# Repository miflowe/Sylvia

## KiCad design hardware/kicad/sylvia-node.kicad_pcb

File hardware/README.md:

# Sylvia Node hardware

Home wildfire-smoke and smoulder sensor for the Sylvia app. **Tier B "Resilient home"** is the board being
built: ESP32-S3 + RAK3172 LoRaWAN backup, Sensirion SEN66, SPEC CO cell + LMP91000, BME688, solar charging
into 2× LiFePO4 18650, 4-layer PCB for JLCPCB. Status and next steps: **`PROGRESS-hardware.md`**.

## Start here
| You are… | Read |
|---|---|
| Reviewing the design | `docs/requirements.md` → `docs/block-diagram.md` → `docs/reference-circuits.md` → `docs/review-checklist.md` |
| Doing the PCB layout | `docs/layout-guide.md`, then open `kicad/sylvia-node.kicad_pro` in KiCad 9 |
| Writing firmware | `firmware/README.md`, `docs/pin-map.md`, `docs/i2c-map.md` |
| Making the deck slide | `docs/tiers.md` |
| Ordering parts | `parts/parts.csv` (all tiers, LCSC numbers, price snapshot), `kicad/bom-draft.csv` (Tier B board) |

## Folder map
| Path | What |
|---|---|
| `kicad/sylvia_node.py` | **Schematic as code** (SKiDL). The source of truth for the circuit |
| `kicad/sylvia-node.net` | Generated KiCad netlist · `sylvia_node.erc` ERC report · `bom-draft.csv` |
| `kicad/sylvia-node.kicad_pcb` | Starter board (all footprints + nets, unplaced) for the layout |
| `kicad/lib/` | Project library: `sylvia.kicad_sym`, `sylvia.pretty/`, `3dmodels/` |
| `parts/` | `parts.csv`, `datasheets.csv` (URL + sha256), download batch lists |
| `datasheets/` | Local PDFs only (copyrighted, gitignored): `tools/fetch_datasheets.py` re-fetches them |
| `docs/` | Requirements, block diagram, reference circuits, power budget, pin + I2C maps, layout guide, checklists, tiers |
| `firmware/` | ESP-IDF firmware; pure-C logic tested on the host |
| `tools/` | Generators and checks (below) |

## Setup (Windows, once)
```bash
python -m venv hardware/.venv
```
```bash
hardware/.venv/Scripts/python -m pip install easyeda2kicad skidl ziglang pytest
```
KiCad 9.0.x must be installed at `C:/Program Files/KiCad/9.0` (used for its libraries, `kicad-cli` and Python).

## Commands
| Command | Does |
|---|---|
| `hardware/.venv/Scripts/python -I hardware/tools/verify_all.py` | **Every check**: ERC, pin/pad, footprints, pin map, power budget, firmware tests, LCSC numbers |
| `hardware/.venv/Scripts/python -I hardware/kicad/sylvia_node.py` | Regenerate netlist + ERC + draft BOM |
| `python -I hardware/tools/build_parts.py` | Refresh `parts.csv` prices/stock from JLCPCB (snapshot) |
| `python -I hardware/tools/build_library.py` | Rebuild the KiCad library from KiCad + EasyEDA + our own parts |
| `"C:/Program Files/KiCad/9.0/bin/python.exe" hardware/tools/make_starter_pcb.py` | Starter board (refuses to overwrite) |
| `python -I hardware/tools/jlc_export.py` | Gerbers + JLCPCB BOM/CPL from the finished board |
| `python -I hardware/tools/power_budget.py` | Regenerate `docs/power-budget.md` |

## Licences
KiCad library content: CC-BY-SA-4.0 with the KiCad library exception. EasyEDA/LCSC-derived symbols, footprints
and `.wrl` models: LCSC/EasyEDA library terms. Manufacturer STEP models and datasheets stay local (gitignored).
Our own footprints and code: the repository's licence.

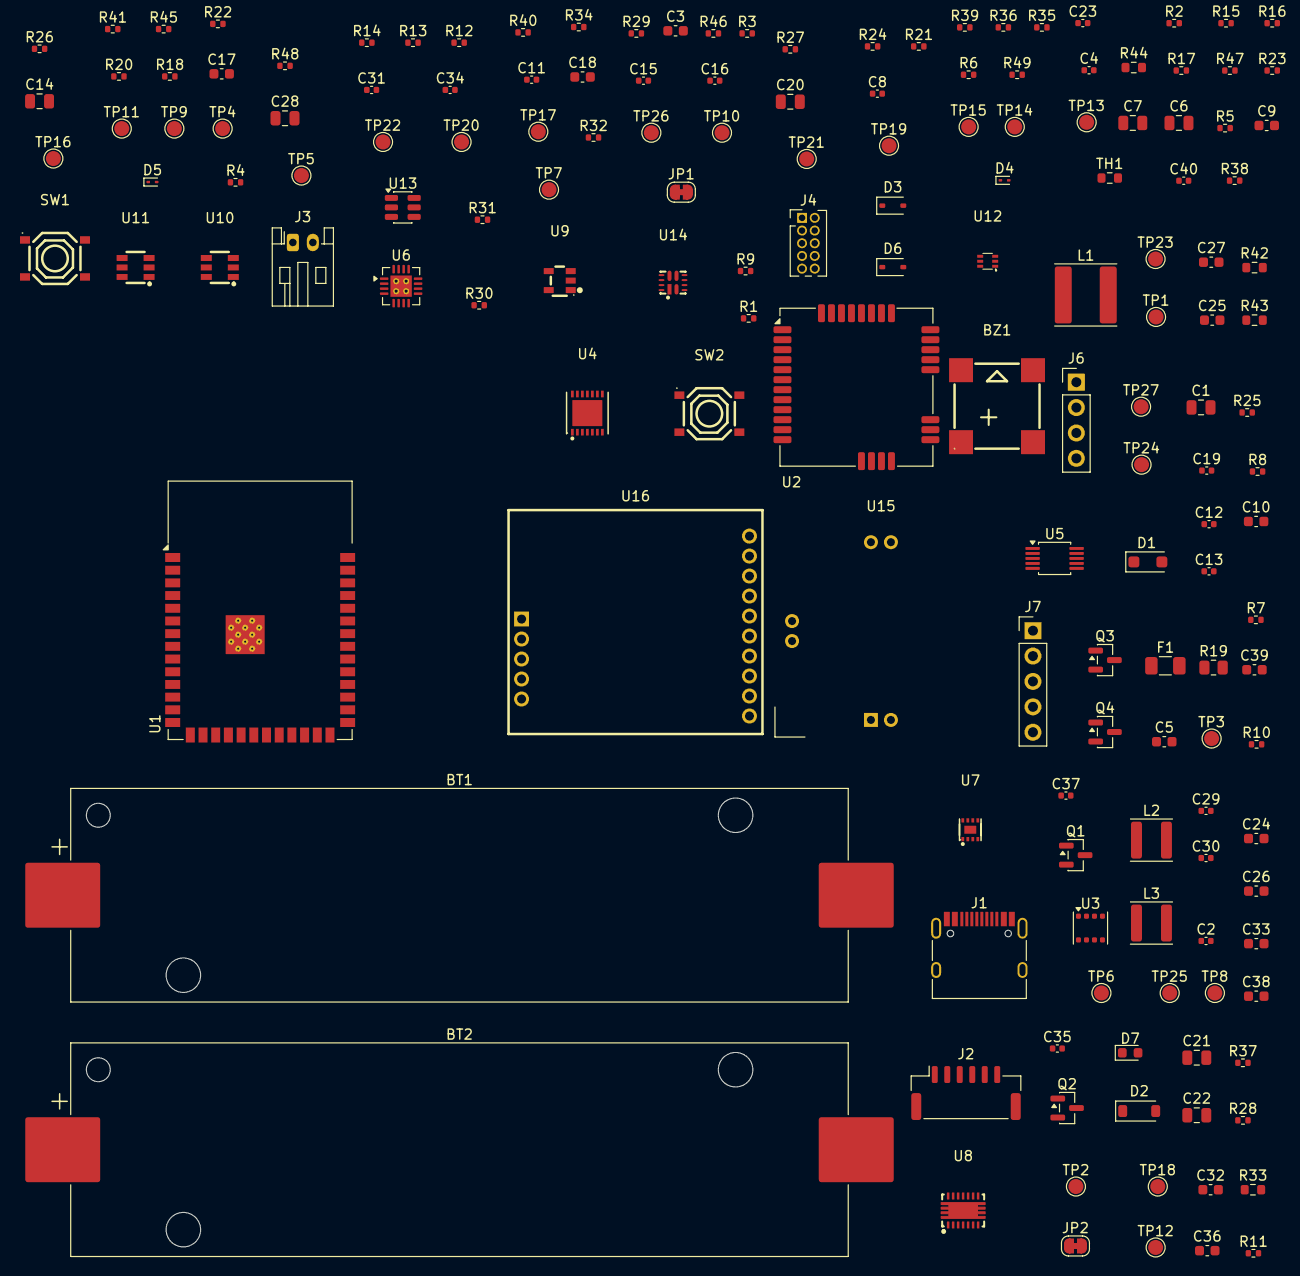
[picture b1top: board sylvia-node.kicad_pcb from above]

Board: 2 copper layers, 161 parts (0 on the bottom side), 88 nets, no tracks yet.

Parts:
BT1, BT2: LiFePO4 18650; BatteryHolder_Keystone_1042_1x18650
BZ1: MLT-8530; BUZ-SMD_4P-L8.5-W8.5-P8.50-BR
C1, C6, C7, C14, C20, C21, C22, C28: 22uF; C_0805_2012Metric
C2, C8, C11, C12, C13, C15, C16, C19, C29, C30, C31, C34, C35, C37, C40: 100nF; C_0402_1005Metric
C3, C9, C10, C24, C26, C33, C38, C39: 1uF; C_0603_1608Metric
C4: 4.7nF; C_0402_1005Metric
C5: 4.7uF; C_0603_1608Metric
C17, C18, C25, C27, C32, C36: 10uF; C_0603_1608Metric
C23: 1nF; C_0402_1005Metric
D1: SMF12A; D_SOD-123F
D2: B5819W; D_SOD-123
D3: 1N5819WS; D_SOD-323
D4, D5: ESD9B5.0ST5G; D_SOD-923
D6: 1N4148WS; D_SOD-323
D7: green; LED_0603_1608Metric
F1: 2A; Fuse_1206_3216Metric
J1: TYPE-C-31-M-12; USB_C_Receptacle_HRO_TYPE-C-31-M-12
J2: SEN66; JST_GH_SM06B-GHS-TB_1x06-1MP_P1.25mm_Horizontal
J3: SOLAR 6V; JST_PH_S2B-PH-K_1x02_P2.00mm_Horizontal
J4: PMSA003I; PinHeader_2x05_P1.27mm_Vertical
J6: UART0; PinHeader_1x04_P2.54mm_Vertical
J7: RAK SWD; PinHeader_1x05_P2.54mm_Vertical
JP1: JP1 VBAT->SYS; SolderJumper-2_P1.3mm_Bridged_RoundedPad1.0x1.5mm
JP2: JP2 3V3 out; SolderJumper-2_P1.3mm_Bridged_RoundedPad1.0x1.5mm
L1: 15uH; L_Sunlord_SWPA6045S
L2: 1.5uH; L_Sunlord_SWPA4020S
L3: 1uH; L_Sunlord_SWPA4020S
Q1, Q2: AO3400A; SOT-23
Q3, Q4: 2N7002; SOT-23
R1, R2, R15, R16, R22, R36, R45, R46: 10k; R_0402_1005Metric
R3, R34, R35, R39, R40: 1k; R_0402_1005Metric
R4: 100R; R_0402_1005Metric
R5, R6, R10, R11, R13, R14, R21, R25, R26, R28, R37, R38, R48: 100k; R_0402_1005Metric
R7, R8: 5.1k; R_0402_1005Metric
R9, R23: 1M; R_0402_1005Metric
R12: 270k; R_0402_1005Metric
R17: 4.42k; R_0402_1005Metric
R18: 21.5k; R_0402_1005Metric
R19: 0.1R; R_0805_2012Metric
R20: 71.5k; R_0402_1005Metric
R24: 180k; R_0402_1005Metric
R27: 732k; R_0402_1005Metric
R29, R30, R31, R32: 4.7k; R_0402_1005Metric
R33, R42, R43, R44: 0R; R_0603_1608Metric
R41: 0R; R_0402_1005Metric
R47: 309k; R_0402_1005Metric
R49: 80.6k; R_0402_1005Metric
SW1: RESET; SW-SMD_4P-L5.1-W5.1-P3.70-LS6.5-TL_H1.5
SW2: BOOT; SW-SMD_4P-L5.1-W5.1-P3.70-LS6.5-TL_H1.5
TH1: 10k B3380; R_0603_1608Metric
TP1: TAMPER; TestPoint_Pad_D1.5mm
TP2: TAMPER_GND; TestPoint_Pad_D1.5mm
TP3: IO48; TestPoint_Pad_D1.5mm
TP4: VBUS; TestPoint_Pad_D1.5mm
TP5: SOLAR_IN; TestPoint_Pad_D1.5mm
TP6: CHG_STAT1; TestPoint_Pad_D1.5mm
TP7: CHG_STAT2; TestPoint_Pad_D1.5mm
TP8: VBAT; TestPoint_Pad_D1.5mm
TP9: VCHG; TestPoint_Pad_D1.5mm
TP10: FG_ALRT; TestPoint_Pad_D1.5mm
TP11: BB_EN; TestPoint_Pad_D1.5mm
TP12: BB_PG; TestPoint_Pad_D1.5mm
TP13: 3V3; TestPoint_Pad_D1.5mm
TP14, TP15: GND; TestPoint_Pad_D1.5mm
TP16: 3V3_SEN; TestPoint_Pad_D1.5mm
TP17: 3V3_ALT; TestPoint_Pad_D1.5mm
TP18: 5V_ALT; TestPoint_Pad_D1.5mm
TP19: I2C1_SDA; TestPoint_Pad_D1.5mm
TP20: I2C1_SCL; TestPoint_Pad_D1.5mm
TP21: I2C0_SDA; TestPoint_Pad_D1.5mm
TP22: I2C0_SCL; TestPoint_Pad_D1.5mm
TP23: 3V3_CO; TestPoint_Pad_D1.5mm
TP24: CO_VOUT; TestPoint_Pad_D1.5mm
TP25: AIN3; TestPoint_Pad_D1.5mm
TP26: LORA_TX; TestPoint_Pad_D1.5mm
TP27: LORA_RX; TestPoint_Pad_D1.5mm
U1: ESP32-S3-WROOM-1-N8R8; ESP32-S3-WROOM-1
U2: RAK3172-9-SM-I; RAK3172
U3: BME688; Bosch_LGA-8_3x3mm_P0.8mm_ClockwisePinNumbering
U4: LMP91000SDX/NOPB; WSON-14_L4.0-W4.0-P0.50-BL-EP-1
U5: ADS1115IDGSR; VSSOP-10_3x3mm_P0.5mm
U6: BQ24650RVAR; Texas_RVA_VQFN-16-1EP_3.5x3.5mm_P0.5mm_EP2.14x2.14mm_Therma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
U7: MAX17048G+T10; TDFN-8_L2.0-W2.0-P0.50-BL-EP1.2
U8: TPS63020DSJR; VSON-14_L4.0-W3.0-P0.50-BL-EP_TI_DSJ
U9: TPS3840PL27; SOT-23-5_L2.9-W1.6-P0.95-LS2.8-BR
U10, U11: TPS22918; SOT-23-6_L2.9-W1.6-P0.95-LS2.8-BR
U12: TPS61023; SOT-563_L1.6-W1.2-P0.50-LS1.6-BR
U13: USBLC6-2SC6; SOT-23-6
U14: TPS2121RUXR; VQFN-HR-12_L2.5-W2.0-P0.50-BL
U15: 110-102; SPEC_110-102_THT
U16: ZE07-CO; SENSOR-TH_ZE07-CO

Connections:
3V3: BZ1.1, C1.1, C2.1, C24.1, C29.1, C30.1, D6.1, J6.1, JP2.2, R1.1, R2.1, R6.1, R15.1, R16.1, R22.1, R31.1, R32.1, R33.1, R36.1, R42.1, TP13.1, U1.2, U3.2, U3.6, U3.8, U10.1, U11.1
3V3_ALT: C26.1, C27.1, L3.1, TP17.1, U11.5, U11.6, U12.2, U12.3
3V3_CO: C31.1, C32.1, C35.1, R33.2, R34.1, TP23.1, U4.6, U5.1, U5.8
3V3_LORA: C36.1, C37.1, J7.1, R42.2, R45.1, U2.24
3V3_REG: C20.1, C21.1, C22.1, JP2.1, R23.1, U8.4, U8.5
3V3_SEN: C25.1, J2.1, J2.6, R29.1, R30.1, TP16.1, U10.5, U10.6
5V_ALT: C28.1, J4.1, J4.2, R27.1, TP18.1, U12.6, U16.15
ADC_AIN3: R38.1, TP25.1, U5.7
ADC_RDY: R36.2, U1.24, U5.2
ALT_UART_RX: R39.2, U1.34
ALT_UART_TX: R40.1, U1.35
BB_EN: TP11.1, U8.12, U9.1
BB_FB: R23.2, R24.1, U8.3
BB_L1: L2.1, U8.8, U8.9
BB_L2: L2.2, U8.6, U8.7
BB_PG: TP12.1, U8.14
BST_FB: R27.2, R28.1, U12.1
BST_SW: L3.2, U12.5
BUZZER: R4.1, U1.8
BUZ_D: BZ1.4, D6.2, Q3.3
BUZ_G: Q3.1, R4.2, R5.1
CC1: J1.A5, R7.1
CC2: J1.B5, R8.1
CHG_BTST: C11.1, D3.1, U6.16
CHG_HIDRV: Q1.1, U6.15
CHG_INHIBIT: Q4.1, R14.1, U1.18
CHG_LODRV: Q2.1, U6.13
CHG_PH: C11.2, L1.1, Q1.2, Q2.3, U6.14
CHG_SRP: C12.1, L1.2, R19.1, U6.10
CHG_STAT1: R15.2, TP6.1, U1.20, U6.3
CHG_STAT2: R16.2, TP7.1, U1.21, U6.5
CHG_TS: R17.2, R18.1, TH1.1, U6.4
CHG_VFB: R20.2, R21.1, U6.8
CO_ADC_ESP: R35.2, U1.39
CO_CE: U4.14, U15.5
CO_RE: U4.13, U15.4
CO_VOUT: R35.1, TP24.1, U4.8, U5.4
CO_WE: U4.12, U15.1, U15.6
EN_ALT: R26.1, U1.17, U11.3
EN_SEN: R25.1, U1.12, U10.3
ESP_BOOT: R2.2, SW2.1, SW2.2, U1.27
ESP_EN: C3.1, R1.2, SW1.1, SW1.2, U1.3
FG_ALRT: R22.2, TP10.1, U1.19, U7.5
GND: BT1.2, BT2.2, C1.2, C2.2, C3.2, C4.2, C5.2, C6.2, C7.2, C8.2, C9.2, C10.2, C13.2, C14.2, C15.2, C16.2, C17.2, C18.2, C19.2, C20.2, C21.2, C22.2, C23.2, C24.2, C25.2, C26.2, C27.2, C28.2, C29.2, C30.2, C31.2, C32.2, C33.2, C35.2, C36.2, C37.2, C38.2, C39.2, C40.2, D1.2, D4.2, D5.2, D7.1, J1.A1, J1.A12, J1.B1, J1.B12, J2.2, J2.5, J2.MP, J3.2, J4.3, J4.4, J6.4, J7.5, Q2.2, Q3.2, Q4.2, R5.2, R7.2, R8.2, R9.2, R11.2, R13.2, R14.2, R18.2, R21.2, R24.2, R25.2, R26.2, R28.2, R37.2, R38.2, R46.2, R48.2, R49.2, SW1.3, SW1.4, SW2.3, SW2.4, TH1.2, TP2.1, TP14.1, TP15.1, U1.1, U1.40, U1.41, U2.11, U2.17, U2.18, U2.23, U2.28, U3.1, U3.5, U3.7, U4.1, U4.2, U4.7, U4.15, U5.3, U6.11, U6.17, U7.1, U7.4, U7.6, U7.9, U8.2, U8.13, U8.15, U9.3, U10.2, U11.2, U12.4, U13.2, U14.3, U14.4, U14.5, U14.9, U14.12, U16.5, U16.14
I2C0_SCL: R32.2, TP22.1, U1.5, U3.4, U4.3, U5.10, U7.7
I2C0_SDA: R31.2, TP21.1, U1.4, U3.3, U4.4, U5.9, U7.8
I2C1_SCL: D5.1, J2.4, J4.7, R30.2, TP20.1, U1.7
I2C1_SDA: D4.1, J2.3, J4.9, R29.2, TP19.1, U1.6
IO48_SPARE: TP3.1, U1.25
LED: R3.1, U1.22
LED_A: D7.2, R3.2
LORA_BOOT0: R46.1, U1.32, U2.21
LORA_RST: J7.4, R45.2, U1.9, U2.22
LORA_RX: R44.2, TP27.1, U1.11
LORA_TX: R43.1, TP26.1, U1.10
LS1_CT: C23.1, U10.4
MPPSET: Q4.3, R12.2, R13.1, U6.2
MUX_ILM: R49.1, U14.10
MUX_PR1: R47.2, R48.1, U14.6
MUX_SS: C40.1, U14.11
PM_SET: J4.10, U1.33
RAK_SWCLK: J7.3, U2.8
RAK_SWDIO: J7.2, U2.7
RAK_UART2_RX: R43.2, U2.1
RAK_UART2_TX: R44.1, U2.2
REGN: C10.1, D3.2, U6.12
SOLAR_IN: D1.1, D2.2, J3.1, TP5.1
SOLAR_MUX: C39.1, D2.1, U14.2
TAMPER: R6.2, TP1.1, U1.23
TIA_C1: C34.1, U4.10
TIA_C2: C34.2, U4.9
UART0_RX: J6.3, U1.36
UART0_TX: J6.2, U1.37
USB_D+: J1.A6, J1.B6, U1.14, U13.3, U13.4
USB_D-: J1.A7, J1.B7, U1.13, U13.1, U13.6
USB_SHIELD: C4.1, J1.S1, R9.1
VBAT: C12.2, C13.1, C14.1, C15.1, C16.1, F1.2, JP1.1, R19.2, R20.1, TP8.1, U6.9, U7.2, U7.3, U9.2
VBAT_SYS: C17.1, C18.1, C19.1, JP1.2, U8.1, U8.10, U8.11
VBUS: C5.1, C38.1, J1.A4, J1.A9, J1.B4, J1.B9, R10.1, R47.1, TP4.1, U13.5, U14.7
VBUS_DET: R10.2, R11.1, U1.31
VCELL: BT1.1, BT2.1, F1.1
VCHG: C6.1, C7.1, C8.1, Q1.3, R12.1, TP9.1, U6.1, U14.1, U14.8
VREF_BQ: C9.1, R17.1, U6.6, U6.7
VREF_CO: C33.1, R34.2, U4.11, U5.5
ZE07_ADC_ESP: R41.2, U1.38
ZE07_DAC: R37.1, R41.1, U5.6, U16.10
ZE07_RXD: R40.2, U16.7
ZE07_TXD: R39.1, U16.8

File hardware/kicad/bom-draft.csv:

Comment,Designator,Footprint,LCSC,Qty,DNP
LiFePO4 18650,"BT1,BT2",BatteryHolder_Keystone_1042_1x18650,C5249310,2,
MLT-8530,BZ1,BUZ-SMD_4P-L8.5-W8.5-P8.50-BR,C94599,1,DNP
22uF,"C1,C6,C7,C14,C20,C21,C22",C_0805_2012Metric,C45783,7,
10uF,"C17,C18,C25,C32,C36",C_0603_1608Metric,C19702,5,
100nF,"C2,C8,C11,C12,C13,C15,C16,C19,C29,C30,C31,C35,C37,C40",C_0402_1005Metric,C1525,14,
1nF,C23,C_0402_1005Metric,C1523,1,
10uF,C27,C_0603_1608Metric,C19702,1,DNP
22uF,C28,C_0805_2012Metric,C45783,1,DNP
1uF,"C3,C9,C10,C24,C26,C33,C38,C39",C_0603_1608Metric,C15849,8,
100nF,C34,C_0402_1005Metric,C1525,1,DNP
4.7nF,C4,C_0402_1005Metric,C1538,1,
4.7uF,C5,C_0603_1608Metric,C19666,1,
SMF12A,D1,D_SOD-123F,C123800,1,
B5819W,D2,D_SOD-123,C8598,1,
1N5819WS,D3,D_SOD-323,C191023,1,
ESD9B5.0ST5G,"D4,D5",D_SOD-923,C111566,2,
1N4148WS,D6,D_SOD-323,C2128,1,DNP
green,D7,LED_0603_1608Metric,C12624,1,
2A,F1,Fuse_1206_3216Metric,C3105,1,
TYPE-C-31-M-12,J1,USB_C_Receptacle_HRO_TYPE-C-31-M-12,C165948,1,
SEN66,J2,JST_GH_SM06B-GHS-TB_1x06-1MP_P1.25mm_Horizontal,C133065,1,
SOLAR 6V,J3,JST_PH_S2B-PH-K_1x02_P2.00mm_Horizontal,C173752,1,
PMSA003I,J4,PinHeader_2x05_P1.27mm_Vertical,,1,DNP
UART0,J6,PinHeader_1x04_P2.54mm_Vertical,,1,
RAK SWD,J7,PinHeader_1x05_P2.54mm_Vertical,,1,
JP1 VBAT->SYS,JP1,SolderJumper-2_P1.3mm_Bridged_RoundedPad1.0x1.5mm,,1,
JP2 3V3 out,JP2,SolderJumper-2_P1.3mm_Bridged_RoundedPad1.0x1.5mm,,1,
15uH,L1,L_Sunlord_SWPA6045S,C83374,1,
1.5uH,L2,L_Sunlord_SWPA4020S,C42099,1,
1uH,L3,L_Sunlord_SWPA4020S,C91254,1,DNP
AO3400A,"Q1,Q2",SOT-23,C20917,2,
2N7002,Q3,SOT-23,C8545,1,DNP
2N7002,Q4,SOT-23,C8545,1,
10k,"R1,R2,R15,R16,R22,R36,R45,R46",R_0402_1005Metric,C25744,8,
270k,R12,R_0402_1005Metric,C25770,1,
4.42k,R17,R_0402_1005Metric,C52269,1,
21.5k,R18,R_0402_1005Metric,C25872,1,
0.1R,R19,R_0805_2012Metric,C127687,1,
71.5k,R20,R_0402_1005Metric,C43534,1,
180k,R24,R_0402_1005Metric,C25760,1,
732k,R27,R_0402_1005Metric,C27016,1,DNP
4.7k,"R29,R30,R31,R32",R_0402_1005Metric,C25900,4,
1k,"R3,R34,R35",R_0402_1005Metric,C11702,3,
0R,"R33,R42,R43,R44",R_0603_1608Metric,C21189,4,
1k,"R39,R40",R_0402_1005Metric,C11702,2,DNP
100R,R4,R_0402_1005Metric,C25076,1,DNP
0R,R41,R_0402_1005Metric,C17168,1,DNP
309k,R47,R_0402_1005Metric,C122546,1,
80.6k,R49,R_0402_1005Metric,C25921,1,
100k,"R5,R28",R_0402_1005Metric,C25741,2,DNP
100k,"R6,R10,R11,R13,R14,R21,R25,R26,R37,R38,R48",R_0402_1005Metric,C25741,11,
5.1k,"R7,R8",R_0402_1005Metric,C25905,2,
1M,"R9,R23",R_0402_1005Metric,C26083,2,
RESET,SW1,SW-SMD_4P-L5.1-W5.1-P3.70-LS6.5-TL_H1.5,C318884,1,
BOOT,SW2,SW-SMD_4P-L5.1-W5.1-P3.70-LS6.5-TL_H1.5,C318884,1,
10k B3380,TH1,R_0603_1608Metric,C13564,1,
TAMPER,TP1,TestPoint_Pad_D1.5mm,,1,
FG_ALRT,TP10,TestPoint_Pad_D1.5mm,,1,
BB_EN,TP11,TestPoint_Pad_D1.5mm,,1,
BB_PG,TP12,TestPoint_Pad_D1.5mm,,1,
3V3,TP13,TestPoint_Pad_D1.5mm,,1,
GND,"TP14,TP15",TestPoint_Pad_D1.5mm,,2,
3V3_SEN,TP16,TestPoint_Pad_D1.5mm,,1,
3V3_ALT,TP17,TestPoint_Pad_D1.5mm,,1,
5V_ALT,TP18,TestPoint_Pad_D1.5mm,,1,
I2C1_SDA,TP19,TestPoint_Pad_D1.5mm,,1,
TAMPER_GND,TP2,TestPoint_Pad_D1.5mm,,1,
I2C1_SCL,TP20,TestPoint_Pad_D1.5mm,,1,
I2C0_SDA,TP21,TestPoint_Pad_D1.5mm,,1,
I2C0_SCL,TP22,TestPoint_Pad_D1.5mm,,1,
3V3_CO,TP23,TestPoint_Pad_D1.5mm,,1,
CO_VOUT,TP24,TestPoint_Pad_D1.5mm,,1,
AIN3,TP25,TestPoint_Pad_D1.5mm,,1,
LORA_TX,TP26,TestPoint_Pad_D1.5mm,,1,
LORA_RX,TP27,TestPoint_Pad_D1.5mm,,1,
IO48,TP3,TestPoint_Pad_D1.5mm,,1,
VBUS,TP4,TestPoint_Pad_D1.5mm,,1,
SOLAR_IN,TP5,TestPoint_Pad_D1.5mm,,1,
CHG_STAT1,TP6,TestPoint_Pad_D1.5mm,,1,
CHG_STAT2,TP7,TestPoint_Pad_D1.5mm,,1,
VBAT,TP8,TestPoint_Pad_D1.5mm,,1,
VCHG,TP9,TestPoint_Pad_D1.5mm,,1,
ESP32-S3-WROOM-1-N8R8,U1,ESP32-S3-WROOM-1,C2913201,1,
TPS22918,"U10,U11",SOT-23-6_L2.9-W1.6-P0.95-LS2.8-BR,C131941,2,
TPS61023,U12,SOT-563_L1.6-W1.2-P0.50-LS1.6-BR,C919459,1,DNP
USBLC6-2SC6,U13,SOT-23-6,C7519,1,
TPS2121RUXR,U14,VQFN-HR-12_L2.5-W2.0-P0.50-BL,C485916,1,
110-102,U15,SPEC_110-102_THT,,1,
ZE07-CO,U16,SENSOR-TH_ZE07-CO,C141345,1,DNP
RAK3172-9-SM-I,U2,RAK3172,C19723905,1,
BME688,U3,Bosch_LGA-8_3x3mm_P0.8mm_ClockwisePinNumbering,C3664478,1,
LMP91000SDX/NOPB,U4,WSON-14_L4.0-W4.0-P0.50-BL-EP-1,C2651584,1,
ADS1115IDGSR,U5,VSSOP-10_3x3mm_P0.5mm,C37593,1,
BQ24650RVAR,U6,Texas_RVA_VQFN-16-1EP_3.5x3.5mm_P0.5mm_EP2.14x2.14mm_ThermalVias,C53712,1,
MAX17048G+T10,U7,TDFN-8_L2.0-W2.0-P0.50-BL-EP1.2,C2682616,1,
TPS63020DSJR,U8,VSON-14_L4.0-W3.0-P0.50-BL-EP_TI_DSJ,C15483,1,
TPS3840PL27,U9,SOT-23-5_L2.9-W1.6-P0.95-LS2.8-BR,C2066421,1,

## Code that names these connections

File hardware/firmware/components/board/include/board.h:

// Sylvia Node Tier B pin map. Names match the schematic nets (kicad/sylvia_node.py);
// tools/pin_map.py fails if this file and the netlist disagree.
#pragma once

#include "driver/gpio.h"

#define PIN_I2C0_SDA GPIO_NUM_4     // on-board bus: BME688 0x76, LMP91000 0x48, ADS1115 0x49, MAX17048 0x36
#define PIN_I2C0_SCL GPIO_NUM_5
#define PIN_I2C1_SDA GPIO_NUM_6     // SEN66 cable bus (pull-ups on the switched 3V3_SEN rail)
#define PIN_I2C1_SCL GPIO_NUM_7
#define I2C_FREQ_HZ 100000          // LMP91000 and SEN66 are both 100 kHz parts

#define PIN_EN_SEN GPIO_NUM_8       // load switch LS1: SEN66 rail (RTC GPIO: held through deep sleep)
#define PIN_EN_ALT GPIO_NUM_9       // load switch LS2: alternates rail (5 V boost)
#define PIN_CHG_INHIBIT GPIO_NUM_10 // high = BQ24650 charging disabled
#define PIN_FG_ALRT GPIO_NUM_11     // MAX17048 ALRT, active low, ext1 wake
#define PIN_CHG_STAT1 GPIO_NUM_12   // low = charging
#define PIN_CHG_STAT2 GPIO_NUM_13   // low = charge done
#define PIN_LED GPIO_NUM_14
#define PIN_BUZZER GPIO_NUM_15      // DNP on the default build
#define PIN_LORA_RST GPIO_NUM_16    // RAK3172 NRST, drive open-drain
#define PIN_LORA_TX GPIO_NUM_17     // ESP32 TX -> RAK3172 UART2 RX
#define PIN_LORA_RX GPIO_NUM_18     // ESP32 RX <- RAK3172 UART2 TX
#define PIN_TAMPER GPIO_NUM_21      // closed lid switch = low, ext1 wake
#define PIN_VBUS_DET GPIO_NUM_38
#define PIN_LORA_BOOT0 GPIO_NUM_39
#define PIN_PM_SET GPIO_NUM_40      // PMSA003I alternate
#define PIN_ALT_UART_RX GPIO_NUM_41 // ZE07-CO alternate
#define PIN_ALT_UART_TX GPIO_NUM_42
#define PIN_ADC_RDY GPIO_NUM_47     // ADS1115 ALERT/RDY
#define PIN_CO_ADC_ESP GPIO_NUM_1   // backup: CO_VOUT on ADC1_CH0

#define LORA_UART_NUM UART_NUM_1
#define LORA_UART_BAUD 115200

// Never use GPIO26-37 (flash + octal PSRAM) or the strapping pins GPIO3/45/46.
